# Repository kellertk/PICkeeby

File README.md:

# PICkeeby

PS/2 Keyboard/Mouse Controller for Homebrew Computers

## Overview

PICkeeby emulates an i8042 keyboard controller, bridging PS/2 devices to a host
computer's I/O bus. It supports both 6502 and Z80 bus timing via a mode jumper,
and handles two PS/2 ports (keyboard and mouse) simultaneously.

The name is a nod to PIC's origin as "Peripheral Interface Controller" -- using
a small microcontroller for I/O duties is a time-honored tradition in computer
design.

## Hardware

- **MCU:** PIC16F18344 at 32 MHz (internal oscillator)
- **GAL:** ATF22V10C for address decoding, status flags (OBF/IBF), A0
  registration, and IRQ generation
- **Latches:** 74AHCT574 (output) and 74AHCT373 (input) for bus interfacing
- **Inverter:** 74AHCT1G14 derives the GAL register clock from the bus clock

Accent on the "homebrew" -- this is a through-hole design on a two-layer PCB.
Accent on the "HC" -- the bus interface is 5V TTL compatible.

### Bus Compatibility

The MODE jumper selects between:

- **6502 mode:** active-high clock (PHI2), active-high R/W
- **Z80 mode:** active-low /WR, active-low /RD

No minimum bus speed -- the design supports fully static operation. Maximum bus
speed is approximately 33 MHz (limited by GAL propagation delay).

## Building

Requires XC8 (Microchip C compiler) and galette (PLD assembler). Run
`./configure` (or `.\configure.ps1` on Windows) first to detect tools and
generate `config.mk`.

```shell
make              # Build firmware + PLD
make firmware     # Build PIC firmware only
make pld          # Build GAL/PLD only
make lint         # Lint markdown files
make flash        # Flash firmware via MPLAB IPE
make flash-pld    # Flash GAL via minipro
```

## Theory of Operation

The host computer sees two I/O ports at consecutive addresses:

- **Port 0x60 (A0=0):** Data register (read/write)
- **Port 0x64 (A0=1):** Status register (read) / Command register (write)

This matches the standard i8042 keyboard controller interface.

### Data Flow

**PS/2 device to host:** PS/2 clock edges trigger an interrupt-on-change ISR
that shifts in scan code bytes. The i8042 emulation layer queues them for the
host. When the output latch is free, a byte is clocked into the 74HCT574 and OBF
(Output Buffer Full) is set in the GAL, asserting /IRQ.

**Host to PS/2 device:** The host writes to the data or command register. The
GAL captures IBF (Input Buffer Full) and A0 on the bus clock edge. The PIC polls
IBF, reads the byte from the 74HCT373 input latch, and routes it through the
i8042 command processor.

### i8042 Emulation

Supports the standard command set: read/write command byte, port enable/disable,
self-test, port test, write to auxiliary device, and read/write of 32 bytes of
EEPROM-backed internal RAM. Scan code translation and A20 gate control are not
implemented.

## Documentation

- [Firmware Design](src/FIRMWARE.md) -- module details, state machines, pin
  assignments, timing
- [Hardware Design](hardware/HARDWARE.md) -- schematic walkthrough, GAL
  equations, connector pinouts

## License

This work is licensed under [CC BY-NC-SA 4.0](LICENSE). This license does not
permit commercial use.

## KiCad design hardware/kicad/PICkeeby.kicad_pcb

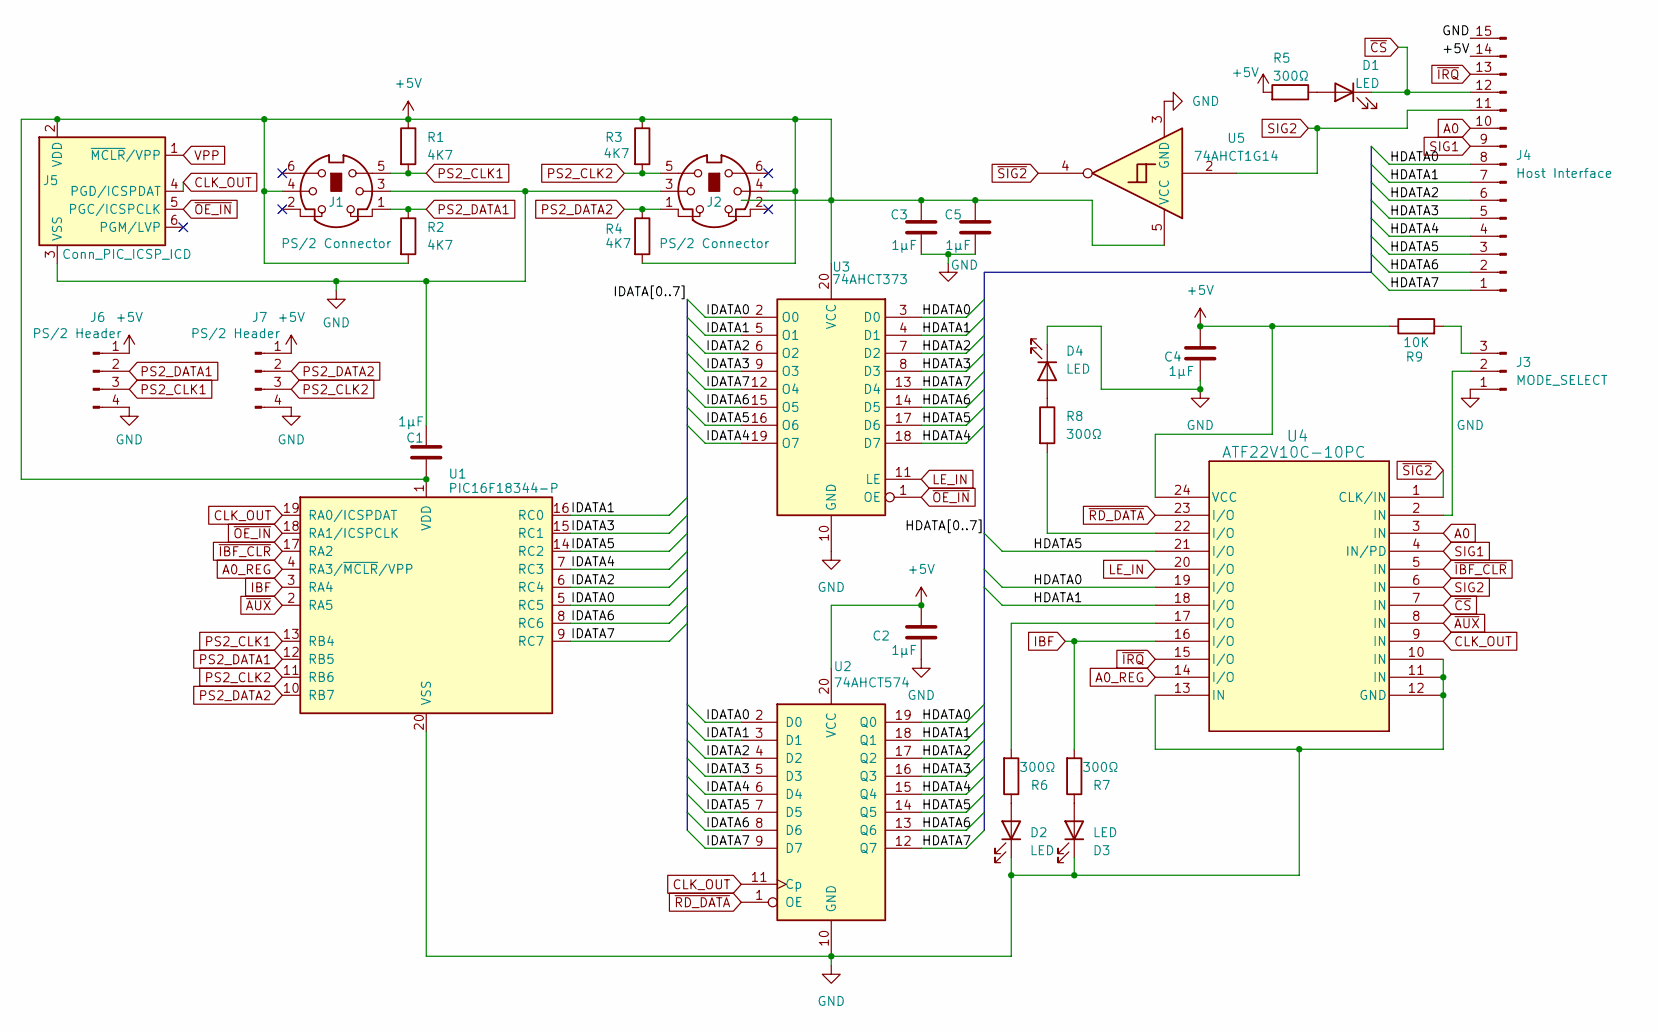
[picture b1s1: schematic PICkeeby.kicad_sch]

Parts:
C1, C2, C3, C4, C5: 1µF; C_0805_2012Metric_Pad1.18x1.45mm_HandSolder
D1, D2, D3, D4: LED; LED_D3.0mm_FlatTop
J1, J2: PS/2 Connector; CUI_MD-60SM
J3: MODE_SELECT; PinHeader_1x03_P2.54mm_Vertical
J4: Host Interface; PinSocket_1x15_P2.54mm_Vertical
J5: Conn_PIC_ICSP_ICD; PinHeader_1x06_P2.54mm_Vertical
J6, J7: PS/2 Header; PinHeader_1x04_P2.54mm_Vertical
R1, R2, R3, R4: 4K7; R_0805_2012Metric_Pad1.20x1.40mm_HandSolder
R5, R6, R7, R8: 300Ω; R_0805_2012Metric_Pad1.20x1.40mm_HandSolder
R9: 10K; R_0805_2012Metric_Pad1.20x1.40mm_HandSolder
U1: PIC16F18344-P; DIP-20_W7.62mm_Socket_LongPads
U2: 74AHCT574; SOIC-20W_7.5x12.8mm_P1.27mm
U3: 74AHCT373; SOIC-20W_7.5x12.8mm_P1.27mm
U4: ATF22V10C-10PC; DIP-24_W7.62mm_Socket_LongPads
U5: 74AHCT1G14; SOT-23-5_HandSoldering

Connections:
+5V: C1.1, C2.1, C3.1, C4.1, C5.1, J1.4, J2.4, J4.14, J5.2 (VDD), J6.1, J7.1, R1.1, R2.2, R3.1, R4.2, R5.2, R9.1, U1.1 (VDD), U2.20 (VCC), U3.20 (VCC), U4.24 (VCC), U5.5 (VCC); also elsewhere on the board
/HDATA0: J4.8, U2.19 (Q0), U3.3 (D0), U4.19 (I/O)
/HDATA1: J4.7, U2.18 (Q1), U3.4 (D1), U4.18 (I/O)
/HDATA2: J4.6, U2.17 (Q2), U3.7 (D2)
/HDATA3: J4.5, U2.16 (Q3), U3.8 (D3)
/HDATA4: J4.4, U2.15 (Q4), U3.18 (D7)
/HDATA5: J4.3, U2.14 (Q5), U3.17 (D6), U4.21 (I/O)
/HDATA6: J4.2, U2.13 (Q6), U3.14 (D5)
/HDATA7: J4.1, U2.12 (Q7), U3.13 (D4)
/IDATA0: U1.5 (RC5), U2.2 (D0), U3.2 (O0)
/IDATA1: U1.16 (RC0), U2.3 (D1), U3.5 (O1)
/IDATA2: U1.6 (RC4), U2.4 (D2), U3.6 (O2)
/IDATA3: U1.15 (RC1), U2.5 (D3), U3.9 (O3)
/IDATA4: U1.7 (RC3), U2.6 (D4), U3.19 (O7)
/IDATA5: U1.14 (RC2), U2.7 (D5), U3.16 (O6)
/IDATA6: U1.8 (RC6), U2.8 (D6), U3.15 (O5)
/IDATA7: U1.9 (RC7), U2.9 (D7), U3.12 (O4)
A0: J4.10, U4.3 (IN)
A0_REG: U1.4 (RA3/~MCLR/VPP), U4.14 (I/O)
CLK_OUT: J5.4 (PGD/ICSPDAT), U1.19 (RA0/ICSPDAT), U2.11 (Cp), U4.9 (IN)
GND: C1.2, C2.2, C3.2, C4.2, C5.2, D2.1 (K), D3.1 (K), D4.1 (K), J1.3, J2.3, J3.1, J4.15, J5.3 (VSS), J6.4, J7.4, U1.20 (VSS), U2.10 (GND), U3.10 (GND), U4.10 (IN), U4.11 (IN), U4.12 (GND), U4.13 (IN), U5.3 (GND); also elsewhere on the board
IBF: R7.2, U1.3 (RA4), U4.16 (I/O)
LE_IN: U3.11 (LE), U4.20 (I/O)
unnamed: D1.2 (A), R5.1
unnamed: D2.2 (A), R6.1
unnamed: D3.2 (A), R7.1
unnamed: D4.2 (A), R8.1
unnamed: J3.2, U4.2 (IN)
unnamed: J3.3, R9.2
unnamed: R6.2, U4.17 (I/O)
unnamed: R8.2, U4.22 (I/O)
PS2_CLK1: J1.5, J6.3, R1.2, U1.13 (RB4)
PS2_CLK2: J2.5, J7.3, R3.2, U1.11 (RB6)
PS2_DATA1: J1.1, J6.2, R2.1, U1.12 (RB5)
PS2_DATA2: J2.1, J7.2, R4.1, U1.10 (RB7)
SIG1: J4.9, U4.4 (IN/PD)
SIG2: J4.11, U4.6 (IN), U5.2
VPP: J5.1 (~MCLR/VPP)
~AUX: U1.2 (RA5), U4.8 (IN)
~CS: D1.1 (K), J4.12, U4.7 (IN)
~IBF_CLR: U1.17 (RA2), U4.5 (IN)
~IRQ: J4.13, U4.15 (I/O)
~OE_IN: J5.5 (PGC/ICSPCLK), U1.18 (RA1/ICSPCLK), U3.1 (OE)
~RD_DATA: U2.1 (OE), U4.23 (I/O)
~SIG2: U4.1 (CLK/IN), U5.4

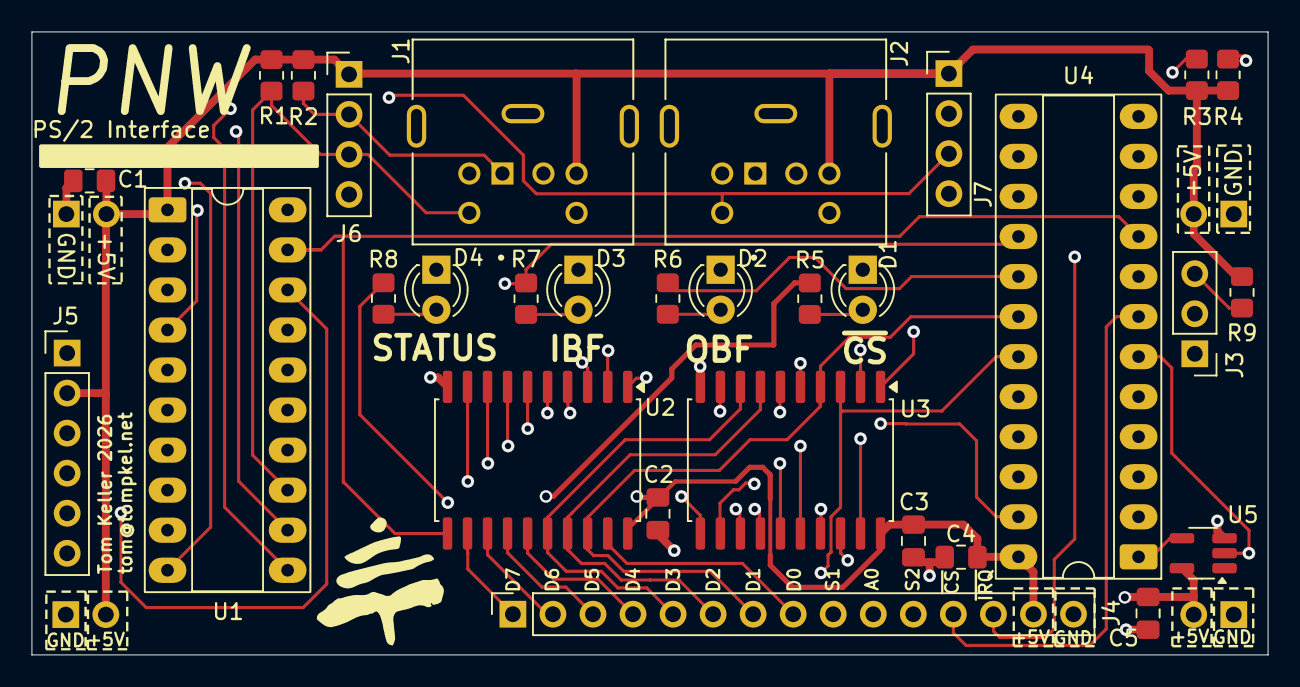
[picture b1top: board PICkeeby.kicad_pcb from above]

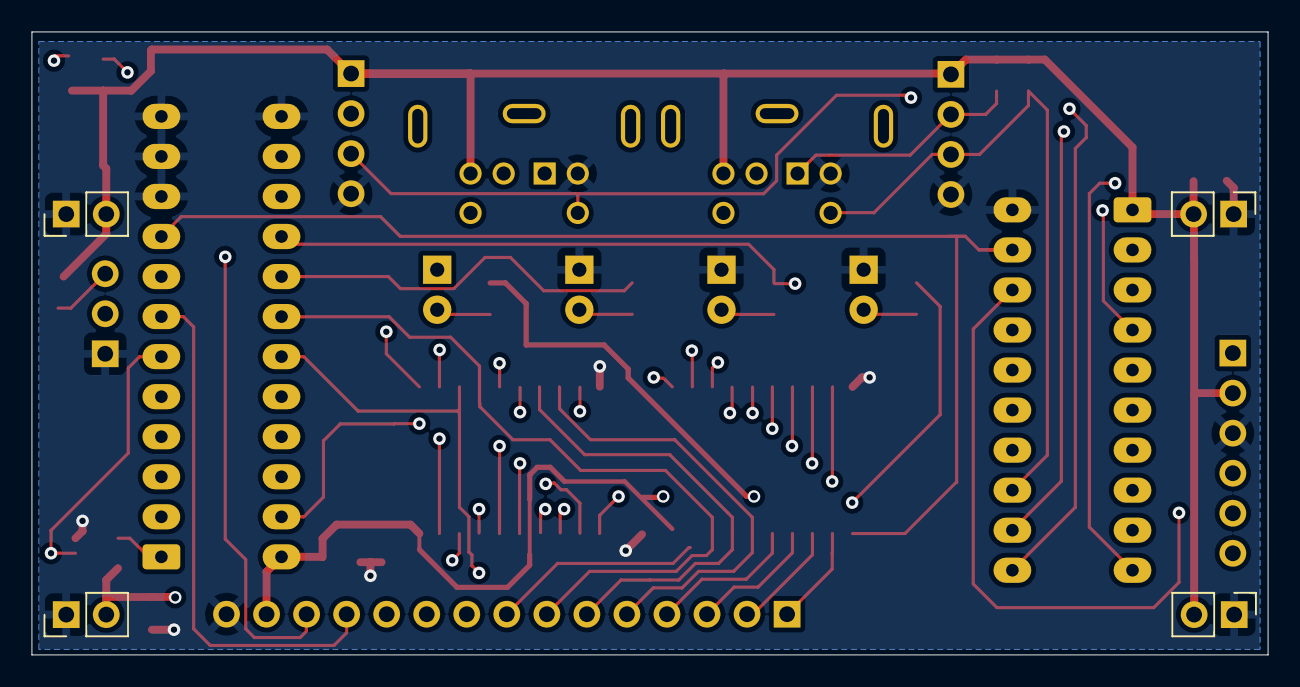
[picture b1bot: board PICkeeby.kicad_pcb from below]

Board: 4 copper layers, 78.4 x 39.5 mm, 34 parts (4 on the bottom side), 44 nets.

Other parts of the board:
x1, x2, x3, x4: PinHeader_1x02_P2.54mm_Vertical

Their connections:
+5V: x1.2, x2.2, x3.2, x4.2; also elsewhere on the board
GND: x1.1, x2.1, x3.1, x4.1; also elsewhere on the board

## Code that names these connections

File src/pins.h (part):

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// RA0 - CLK_OUT
#define CLK_OUT_TRIS                 TRISAbits.TRISA0
#define CLK_OUT_LAT                  LATAbits.LATA0
#define CLK_OUT_PORT                 PORTAbits.RA0
#define CLK_OUT_WPU                  WPUAbits.WPUA0
#define CLK_OUT_OD                   ODCONAbits.ODCA0
#define CLK_OUT_ANS                  ANSELAbits.ANSA0
#define CLK_OUT_SetHigh()            do { LATAbits.LATA0 = 1; } while(0)
#define CLK_OUT_SetLow()             do { LATAbits.LATA0 = 0; } while(0)
#define CLK_OUT_Toggle()             do { LATAbits.LATA0 = ~LATAbits.LATA0; } while(0)
#define CLK_OUT_GetValue()           PORTAbits.RA0
#define CLK_OUT_SetDigitalInput()    do { TRISAbits.TRISA0 = 1; } while(0)
#define CLK_OUT_SetDigitalOutput()   do { TRISAbits.TRISA0 = 0; } while(0)
#define CLK_OUT_SetPullup()          do { WPUAbits.WPUA0 = 1; } while(0)
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// RA1 - OE_INB
#define OE_INB_TRIS                 TRISAbits.TRISA1
#define OE_INB_LAT                  LATAbits.LATA1
#define OE_INB_PORT                 PORTAbits.RA1
#define OE_INB_WPU                  WPUAbits.WPUA1
#define OE_INB_OD                   ODCONAbits.ODCA1
#define OE_INB_ANS                  ANSELAbits.ANSA1
#define OE_INB_SetHigh()            do { LATAbits.LATA1 = 1; } while(0)
#define OE_INB_SetLow()             do { LATAbits.LATA1 = 0; } while(0)
#define OE_INB_Toggle()             do { LATAbits.LATA1 = ~LATAbits.LATA1; } while(0)
#define OE_INB_GetValue()           PORTAbits.RA1
#define OE_INB_SetDigitalInput()    do { TRISAbits.TRISA1 = 1; } while(0)
#define OE_INB_SetDigitalOutput()   do { TRISAbits.TRISA1 = 0; } while(0)
#define OE_INB_SetPullup()          do { WPUAbits.WPUA1 = 1; } while(0)
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// RA2 - IBF_CLRB
#define IBF_CLRB_TRIS                 TRISAbits.TRISA2
#define IBF_CLRB_LAT                  LATAbits.LATA2
#define IBF_CLRB_PORT                 PORTAbits.RA2
#define IBF_CLRB_WPU                  WPUAbits.WPUA2
#define IBF_CLRB_OD                   ODCONAbits.ODCA2
#define IBF_CLRB_ANS                  ANSELAbits.ANSA2
#define IBF_CLRB_SetHigh()            do { LATAbits.LATA2 = 1; } while(0)
#define IBF_CLRB_SetLow()             do { LATAbits.LATA2 = 0; } while(0)
#define IBF_CLRB_Toggle()             do { LATAbits.LATA2 = ~LATAbits.LATA2; } while(0)
#define IBF_CLRB_GetValue()           PORTAbits.RA2
#define IBF_CLRB_SetDigitalInput()    do { TRISAbits.TRISA2 = 1; } while(0)
#define IBF_CLRB_SetDigitalOutput()   do { TRISAbits.TRISA2 = 0; } while(0)
#define IBF_CLRB_SetPullup()          do { WPUAbits.WPUA2 = 1; } while(0)
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
// RA3 - A0 (A0_REG from GAL, directly read)
#define A0_TRIS                 TRISAbits.TRISA3
#define A0_PORT                 PORTAbits.RA3
#define A0_GetValue()           PORTAbits.RA3

// RA4 - IBF (Input Buffer Full from GAL)
#define IBF_TRIS                 TRISAbits.TRISA4
#define IBF_LAT                  LATAbits.LATA4
#define IBF_PORT                 PORTAbits.RA4
#define IBF_WPU                  WPUAbits.WPUA4
#define IBF_OD                   ODCONAbits.ODCA4
#define IBF_ANS                  ANSELAbits.ANSA4
#define IBF_GetValue()           PORTAbits.RA4
#define IBF_SetDigitalInput()    do { TRISAbits.TRISA4 = 1; } while(0)
#define IBF_SetDigitalOutput()   do { TRISAbits.TRISA4 = 0; } while(0)
#define IBF_SetPullup()          do { WPUAbits.WPUA4 = 1; } while(0)
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// RA5 - AUXB
#define AUXB_TRIS                 TRISAbits.TRISA5
#define AUXB_LAT                  LATAbits.LATA5
#define AUXB_PORT                 PORTAbits.RA5
#define AUXB_WPU                  WPUAbits.WPUA5
#define AUXB_OD                   ODCONAbits.ODCA5
#define AUXB_ANS                  ANSELAbits.ANSA5
#define AUXB_SetHigh()            do { LATAbits.LATA5 = 1; } while(0)
#define AUXB_SetLow()             do { LATAbits.LATA5 = 0; } while(0)
#define AUXB_Toggle()             do { LATAbits.LATA5 = ~LATAbits.LATA5; } while(0)
#define AUXB_GetValue()           PORTAbits.RA5
#define AUXB_SetDigitalInput()    do { TRISAbits.TRISA5 = 1; } while(0)
#define AUXB_SetDigitalOutput()   do { TRISAbits.TRISA5 = 0; } while(0)
#define AUXB_SetPullup()          do { WPUAbits.WPUA5 = 1; } while(0)
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// RB4 - PS2_CLK1
#define PS2_CLK1_TRIS                 TRISBbits.TRISB4
#define PS2_CLK1_LAT                  LATBbits.LATB4
#define PS2_CLK1_PORT                 PORTBbits.RB4
#define PS2_CLK1_WPU                  WPUBbits.WPUB4
#define PS2_CLK1_OD                   ODCONBbits.ODCB4
#define PS2_CLK1_ANS                  ANSELBbits.ANSB4
#define PS2_CLK1_SetHigh()            do { LATBbits.LATB4 = 1; } while(0)
#define PS2_CLK1_SetLow()             do { LATBbits.LATB4 = 0; } while(0)
#define PS2_CLK1_Toggle()             do { LATBbits.LATB4 = ~LATBbits.LATB4; } while(0)
#define PS2_CLK1_GetValue()           PORTBbits.RB4
#define PS2_CLK1_SetDigitalInput()    do { TRISBbits.TRISB4 = 1; } while(0)
#define PS2_CLK1_SetDigitalOutput()   do { TRISBbits.TRISB4 = 0; } while(0)
#define PS2_CLK1_SetPullup()          do { WPUBbits.WPUB4 = 1; } while(0)
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// RB5 - PS2_DATA1
#define PS2_DATA1_TRIS                 TRISBbits.TRISB5
#define PS2_DATA1_LAT                  LATBbits.LATB5
#define PS2_DATA1_PORT                 PORTBbits.RB5
#define PS2_DATA1_WPU                  WPUBbits.WPUB5
#define PS2_DATA1_OD                   ODCONBbits.ODCB5
#define PS2_DATA1_ANS                  ANSELBbits.ANSB5
#define PS2_DATA1_SetHigh()            do { LATBbits.LATB5 = 1; } while(0)
#define PS2_DATA1_SetLow()             do { LATBbits.LATB5 = 0; } while(0)
#define PS2_DATA1_Toggle()             do { LATBbits.LATB5 = ~LATBbits.LATB5; } while(0)
#define PS2_DATA1_GetValue()           PORTBbits.RB5
#define PS2_DATA1_SetDigitalInput()    do { TRISBbits.TRISB5 = 1; } while(0)
#define PS2_DATA1_SetDigitalOutput()   do { TRISBbits.TRISB5 = 0; } while(0)
#define PS2_DATA1_SetPullup()          do { WPUBbits.WPUB5 = 1; } while(0)
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// RB6 - PS2_CLK2
#define PS2_CLK2_TRIS                 TRISBbits.TRISB6
#define PS2_CLK2_LAT                  LATBbits.LATB6
#define PS2_CLK2_PORT                 PORTBbits.RB6
#define PS2_CLK2_WPU                  WPUBbits.WPUB6
#define PS2_CLK2_OD                   ODCONBbits.ODCB6
#define PS2_CLK2_ANS                  ANSELBbits.ANSB6
#define PS2_CLK2_SetHigh()            do { LATBbits.LATB6 = 1; } while(0)
#define PS2_CLK2_SetLow()             do { LATBbits.LATB6 = 0; } while(0)
#define PS2_CLK2_Toggle()             do { LATBbits.LATB6 = ~LATBbits.LATB6; } while(0)
#define PS2_CLK2_GetValue()           PORTBbits.RB6
#define PS2_CLK2_SetDigitalInput()    do { TRISBbits.TRISB6 = 1; } while(0)
#define PS2_CLK2_SetDigitalOutput()   do { TRISBbits.TRISB6 = 0; } while(0)
#define PS2_CLK2_SetPullup()          do { WPUBbits.WPUB6 = 1; } while(0)
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// RB7 - PS2_DATA2
#define PS2_DATA2_TRIS                 TRISBbits.TRISB7
#define PS2_DATA2_LAT                  LATBbits.LATB7
#define PS2_DATA2_PORT                 PORTBbits.RB7
#define PS2_DATA2_WPU                  WPUBbits.WPUB7
#define PS2_DATA2_OD                   ODCONBbits.ODCB7
#define PS2_DATA2_ANS                  ANSELBbits.ANSB7
#define PS2_DATA2_SetHigh()            do { LATBbits.LATB7 = 1; } while(0)
#define PS2_DATA2_SetLow()             do { LATBbits.LATB7 = 0; } while(0)
#define PS2_DATA2_Toggle()             do { LATBbits.LATB7 = ~LATBbits.LATB7; } while(0)
#define PS2_DATA2_GetValue()           PORTBbits.RB7
#define PS2_DATA2_SetDigitalInput()    do { TRISBbits.TRISB7 = 1; } while(0)
#define PS2_DATA2_SetDigitalOutput()   do { TRISBbits.TRISB7 = 0; } while(0)
#define PS2_DATA2_SetPullup()          do { WPUBbits.WPUB7 = 1; } while(0)
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// RC6=IDATA6, RC7=IDATA7
#define IDATA1_TRIS                 TRISCbits.TRISC0
#define IDATA1_LAT                  LATCbits.LATC0
#define IDATA1_PORT                 PORTCbits.RC0
#define IDATA1_SetHigh()            do { LATCbits.LATC0 = 1; } while(0)
#define IDATA1_SetLow()             do { LATCbits.LATC0 = 0; } while(0)
#define IDATA1_GetValue()           PORTCbits.RC0
#define IDATA1_SetDigitalInput()    do { TRISCbits.TRISC0 = 1; } while(0)
#define IDATA1_SetDigitalOutput()   do { TRISCbits.TRISC0 = 0; } while(0)

#define IDATA3_TRIS                 TRISCbits.TRISC1
#define IDATA3_LAT                  LATCbits.LATC1
#define IDATA3_PORT                 PORTCbits.RC1
#define IDATA3_SetHigh()            do { LATCbits.LATC1 = 1; } while(0)
#define IDATA3_SetLow()             do { LATCbits.LATC1 = 0; } while(0)
#define IDATA3_GetValue()           PORTCbits.RC1
#define IDATA3_SetDigitalInput()    do { TRISCbits.TRISC1 = 1; } while(0)
#define IDATA3_SetDigitalOutput()   do { TRISCbits.TRISC1 = 0; } while(0)

#define IDATA5_TRIS                 TRISCbits.TRISC2
#define IDATA5_LAT                  LATCbits.LATC2
#define IDATA5_PORT                 PORTCbits.RC2
#define IDATA5_SetHigh()            do { LATCbits.LATC2 = 1; } while(0)
#define IDATA5_SetLow()             do { LATCbits.LATC2 = 0; } while(0)
#define IDATA5_GetValue()           PORTCbits.RC2
#define IDATA5_SetDigitalInput()    do { TRISCbits.TRISC2 = 1; } while(0)
#define IDATA5_SetDigitalOutput()   do { TRISCbits.TRISC2 = 0; } while(0)
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
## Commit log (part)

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2025-12-21 handle additional extended keys
2025-12-21 update numpad keymap
2025-12-23 update configuration bits
2025-12-25 remove dependency on mplab
2025-12-25 add debug led
2025-12-27 wake from sleep takes too long
2025-12-27 fix keymap handling
2025-12-28 fix keymap, support commands
2026-02-24 update gitignore
2026-02-25 change idata pinout
2026-02-26 GAL async reset for IBF clear, doc fixes, linting
    - PLD: Add AR product term for async IBF/A0_REG clear (fixes Z80 deadlock)
    - Firmware: Fix LATA init (OE_INB high at startup), simplify IBF clear
    - Firmware: Move IDATA remap functions from pins.h to host.c
2026-02-26 add license, update readme
